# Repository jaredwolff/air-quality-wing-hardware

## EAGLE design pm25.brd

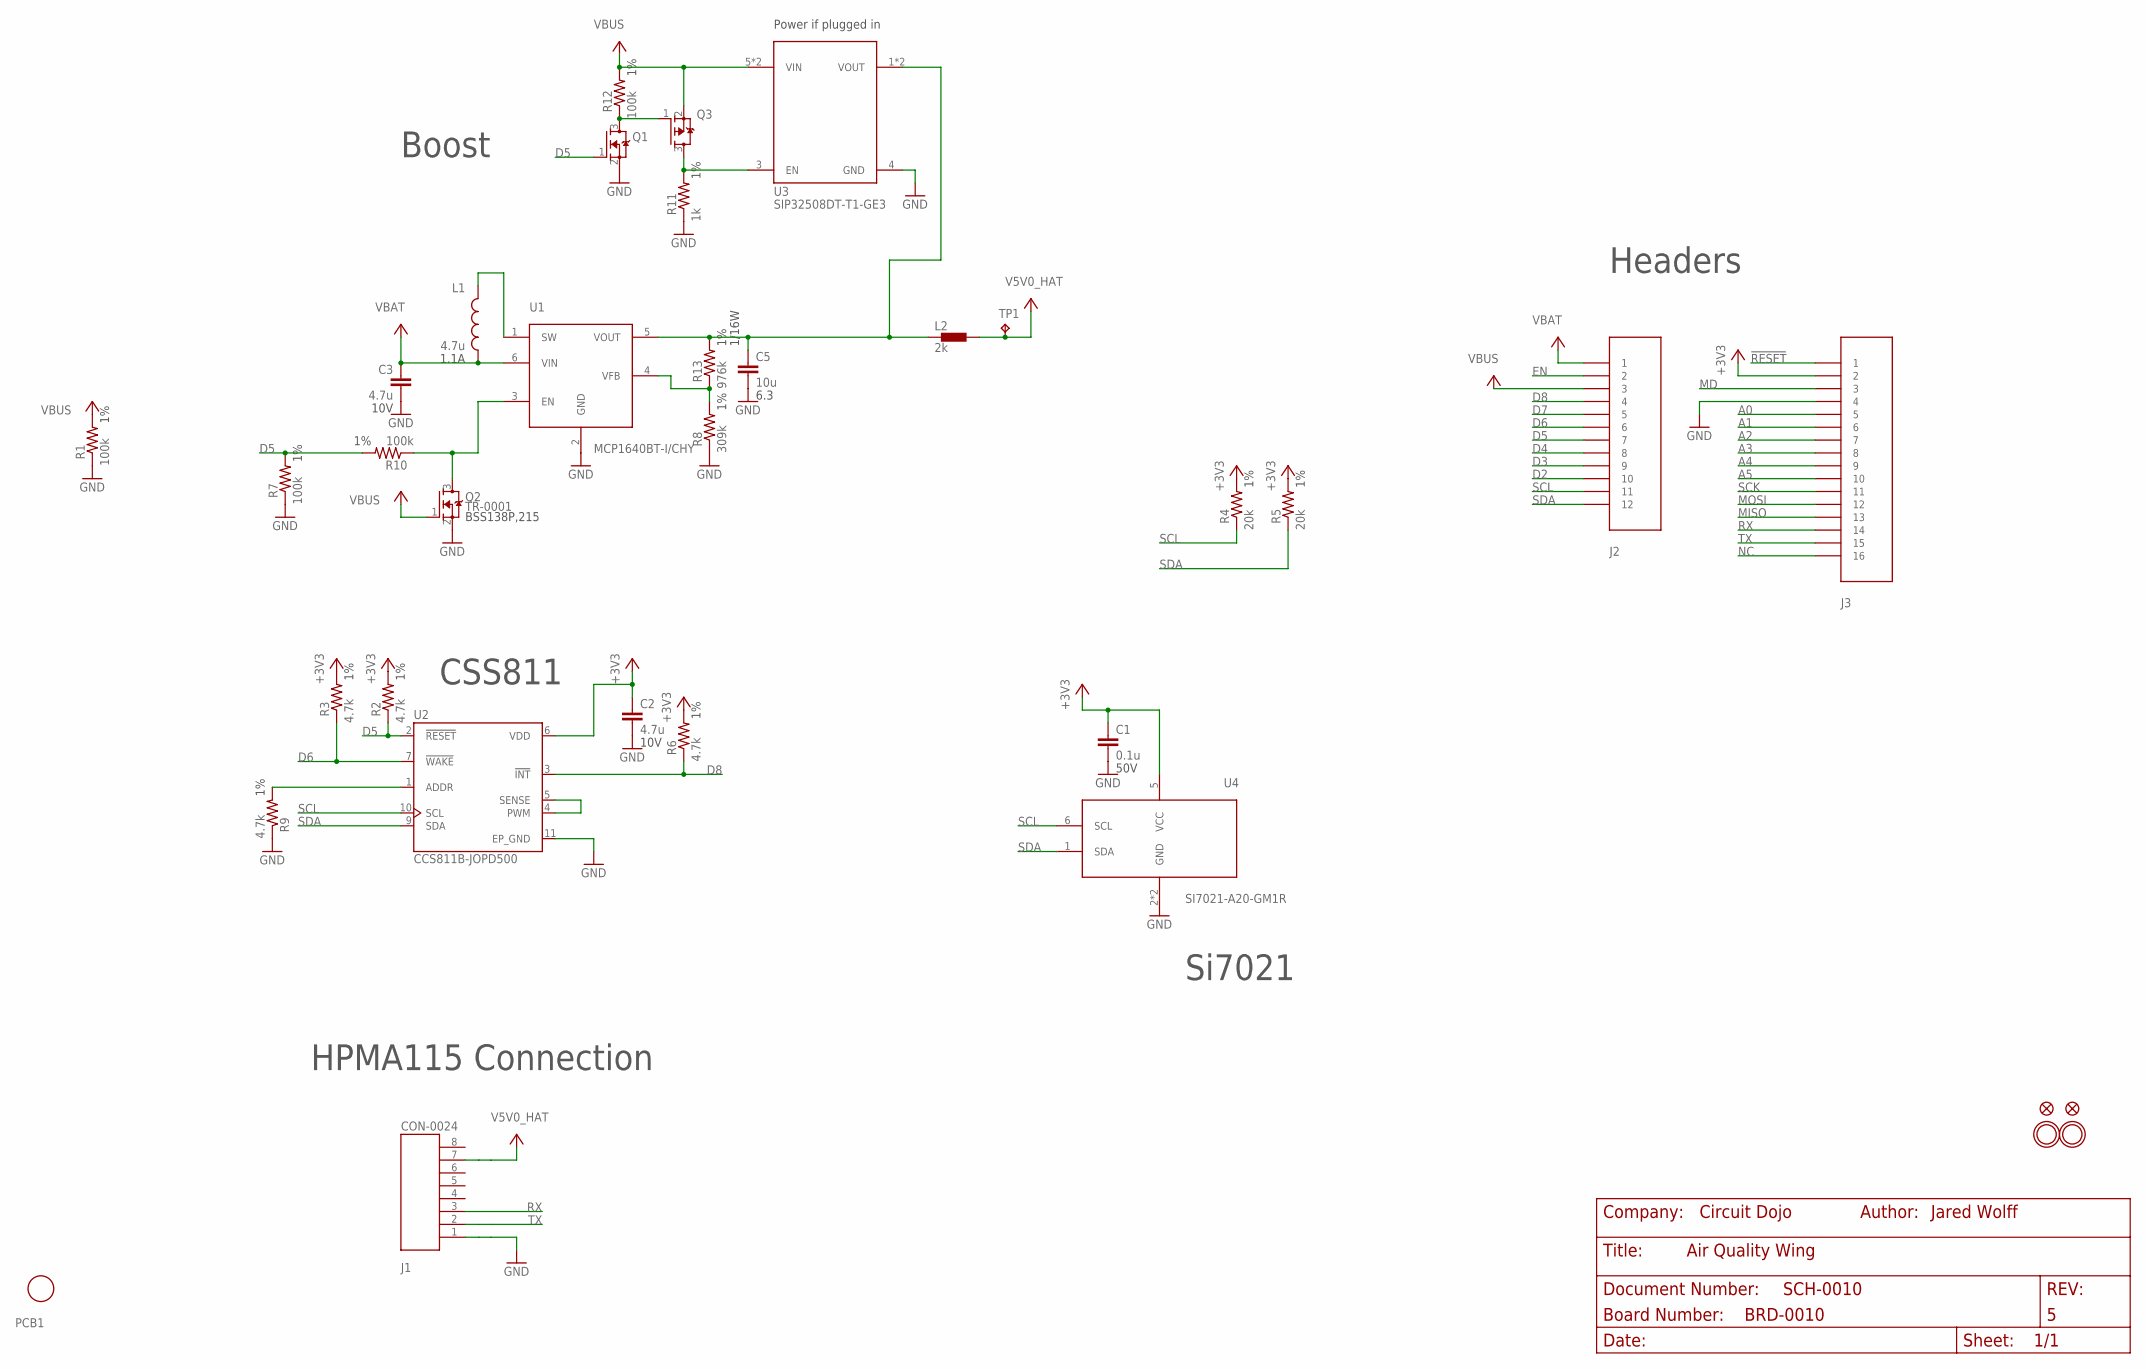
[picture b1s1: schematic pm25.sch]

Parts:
C1: 0.1u; CAPC1005X55N
C2, C3: 4.7u; C0603
C5: 10u; C0603
J1: CON-0024; 0532610871
J2: HEADER-12; CON-HEADER-1X12
J3: HEADER-16; CON-HEADER-1X16
L1: 4.7u; IND-2P0X2P0X1P2
L2: 2k; R0805
PCB1: PCB-PS-CCS811-SI7021; PLACEHOLDER
Q1, Q2: TR-0001; SOT23
Q3: TR-0003; SOT23
R1, R7, R10, R12: 100k; R0402
R2, R3, R6, R9: 4.7k; R0402
R4, R5: 20k; R0402
R8: 309k; R0402
R11: 1k; R0402
R13: 976k; R0402
TP1: TP; TP-1P27
U1: POWER-VREG-FB-EN-SW-350MA; SOT23-6
U2: CCS811B-JOPD500; SON60P400X270X110-11N
U3: POWER-SWITCH-SIP32508-SO23-6; SOT23-6
U4: SI7021-A20-GM1R; SON100P300X300X80-7N
U$31, U$32: MOUNTINGHOLE2.5; MOUNTINGHOLE_2.5_PLATED
U$34, U$35: FIDUCIAL""; FIDUCIAL_1MM

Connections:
!RESET: J3.1
+3V3: C1.1, C2.1, J3.2, R2.2, R3.2, R4.2, R5.2, R6.2, U2.6 (VDD), U4.5 (VCC)
A0: J3.5
A1: J3.6
A2: J3.7
A3: J3.8
A4: J3.9
A5: J3.10
D2: J2.10
D3: J2.9
D4: J2.8
D5: J2.7, Q1.1 (G), R2.1, R7.2, R10.2, U2.2 (!RESET)
D6: J2.6, R3.1, U2.7 (!WAKE)
D7: J2.5
D8: J2.4, R6.1, U2.3 (!INT)
EN: J2.2
GND: C1.2, C2.2, C3.2, C5.2, J1.1, J3.4, Q1.2 (S), Q2.2 (S), R1.1, R7.1, R8.1, R9.1, R11.1, U1.2 (GND), U2.11 (EP_GND), U3.4 (GND), U4.2 (GND), U4.7 (GND)
MD: J3.3
MISO: J3.13
MOSI: J3.12
unnamed: L1.P$1 (1), U1.1 (SW)
unnamed: R8.2, R13.1, U1.4 (VFB)
unnamed: Q1.3 (D), Q3.1 (G), R12.1
unnamed: R9.2, U2.1 (ADDR)
unnamed: U2.4 (PWM), U2.5 (SENSE)
unnamed: Q2.3 (D), R10.1, U1.3 (EN)
unnamed: Q3.3 (D), R11.2, U3.3 (EN)
NC: J3.16
RX: J1.3, J3.14
SCK: J3.11
SCL: J2.11, R4.1, U2.10 (SCL), U4.6 (SCL)
SDA: J2.12, R5.1, U2.9 (SDA), U4.1 (SDA)
TX: J1.2, J3.15
V5V0_BEAD: C5.1, L2.1, R13.2, U1.5 (VOUT), U3.1 (VOUT), U3.2 (VOUT)
V5V0_HAT: J1.7, L2.2, TP1.P$1, TP1.P$2, TP1.TP
VBAT: C3.1, J2.1, L1.P$2 (2), U1.6 (VIN)
VBUS: J2.3, Q2.1 (G), Q3.2 (S), R1.2, R12.2, U3.5 (VIN), U3.6 (VIN)

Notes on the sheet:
Boost
Si7021
CSS811
HPMA115 Connection
Headers
Power if plugged in

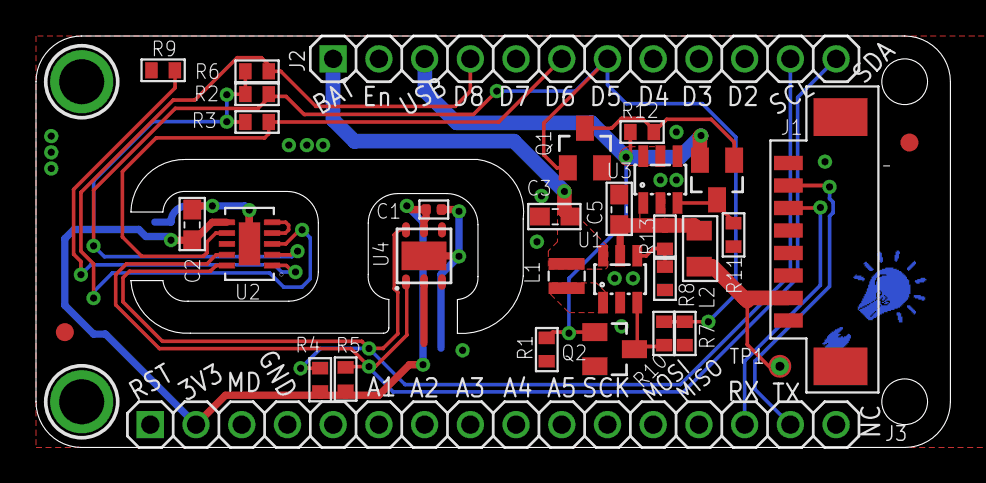
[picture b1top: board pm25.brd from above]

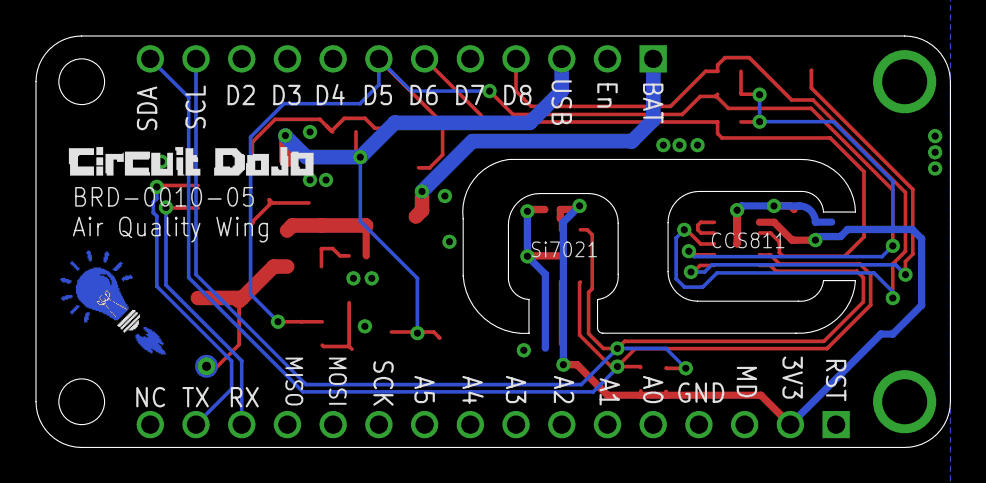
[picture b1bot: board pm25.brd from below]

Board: 2 copper layers, 50.8 x 22.9 mm, 37 parts (2 on the bottom side), 20 nets.

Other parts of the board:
U$1: LOGO-CIRCUITDOJO-BULB
U$2: LOGO-CIRCUITDOJO

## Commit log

2019-10-17 Version 5!
2019-10-21 Renaming to Air Quality Wing

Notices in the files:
parts and their libraries:
microbuilder: This work is placed in the public domain, and may be freely used for commercial and non-commercial work with the following conditions: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
